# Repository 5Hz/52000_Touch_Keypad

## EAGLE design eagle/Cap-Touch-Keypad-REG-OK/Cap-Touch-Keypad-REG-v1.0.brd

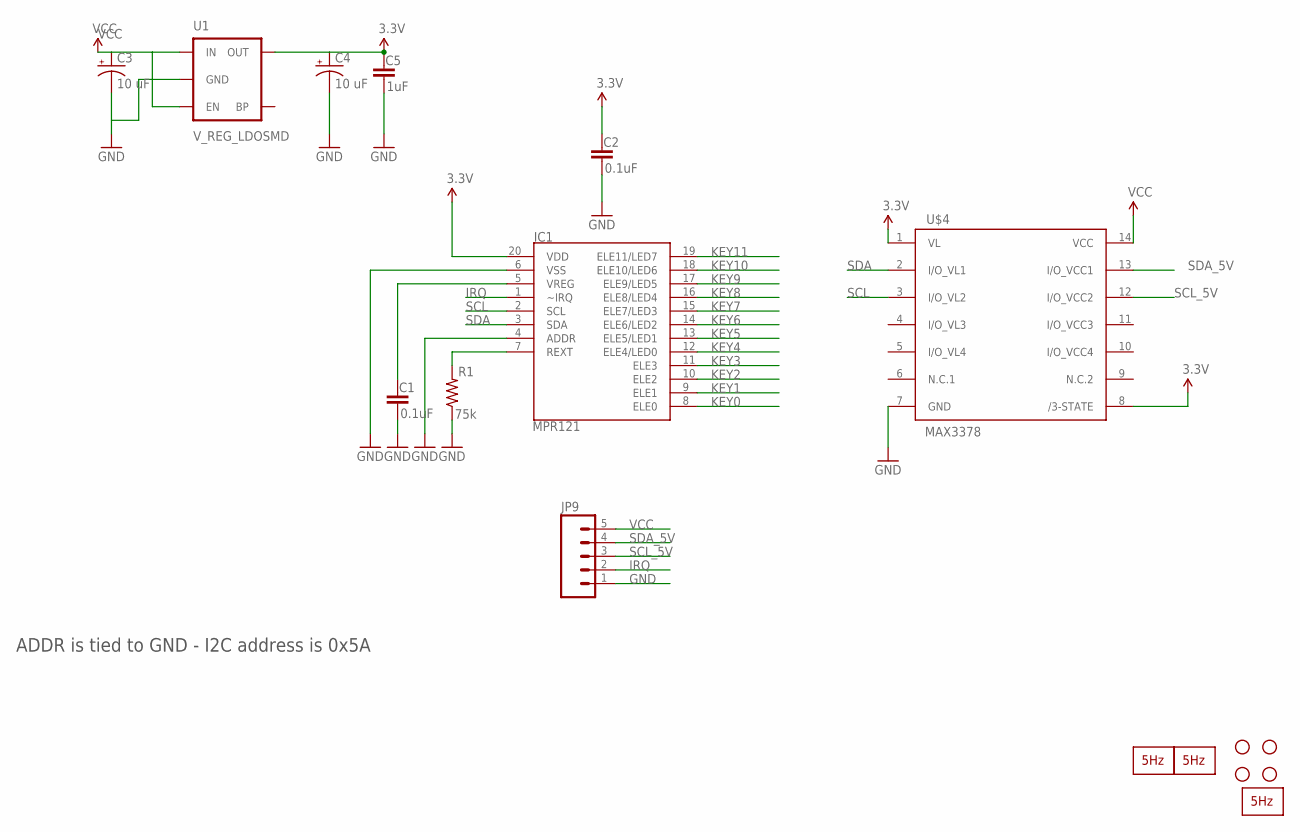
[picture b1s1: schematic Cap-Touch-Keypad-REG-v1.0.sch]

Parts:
C1, C2: 0.1uF; 0402-CAP
C3, C4: 10 uF; EIA3216
C5: 1uF; 0402-CAP
IC1: MPR121; QFN-20-0.4MM
JP3, JP4, JP7, JP8: STAND-OFF
JP9: M05PTH; 1X05
R1: 75k; 0402-RES
U1: V_REG_LDOSMD; SOT23-5
U$1: LOGO2_SILKL20MM; LARGO2_20MM
U$2, U$3: LOGO2_SILKC5MM; CIRCULO2_5MM
U$4: MAX3378; TSSOP14

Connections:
3.3V: C2.1, C4.A (+), C5.1, IC1.20 (VDD), U1.5 (OUT), U$4.1 (VL), U$4.8 (/3-STATE)
GND: C1.2, C2.2, C3.C (-), C4.C (-), C5.2, IC1.4 (ADDR), IC1.6 (VSS), JP9.1, R1.1, U1.2 (GND), U$4.7 (GND)
IRQ: IC1.1 (~IRQ), JP9.2
KEY0: IC1.8 (ELE0)
KEY1: IC1.9 (ELE1)
KEY2: IC1.10 (ELE2)
KEY3: IC1.11 (ELE3)
KEY4: IC1.12 (ELE4/LED0)
KEY5: IC1.13 (ELE5/LED1)
KEY6: IC1.14 (ELE6/LED2)
KEY7: IC1.15 (ELE7/LED3)
KEY8: IC1.16 (ELE8/LED4)
KEY9: IC1.17 (ELE9/LED5)
KEY10: IC1.18 (ELE10/LED6)
KEY11: IC1.19 (ELE11/LED7)
REXT: IC1.7 (REXT), R1.2
SCL: IC1.2 (SCL), U$4.3 (I/O_VL2)
SCL_5V: JP9.3, U$4.12 (I/O_VCC2)
SDA: IC1.3 (SDA), U$4.2 (I/O_VL1)
SDA_5V: JP9.4, U$4.13 (I/O_VCC1)
VCC: C3.A (+), JP9.5, U1.1 (IN), U1.3 (EN), U$4.14 (VCC)
VREG: C1.1, IC1.5 (VREG)

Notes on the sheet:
ADDR is tied to GND - I2C address is 0x5A

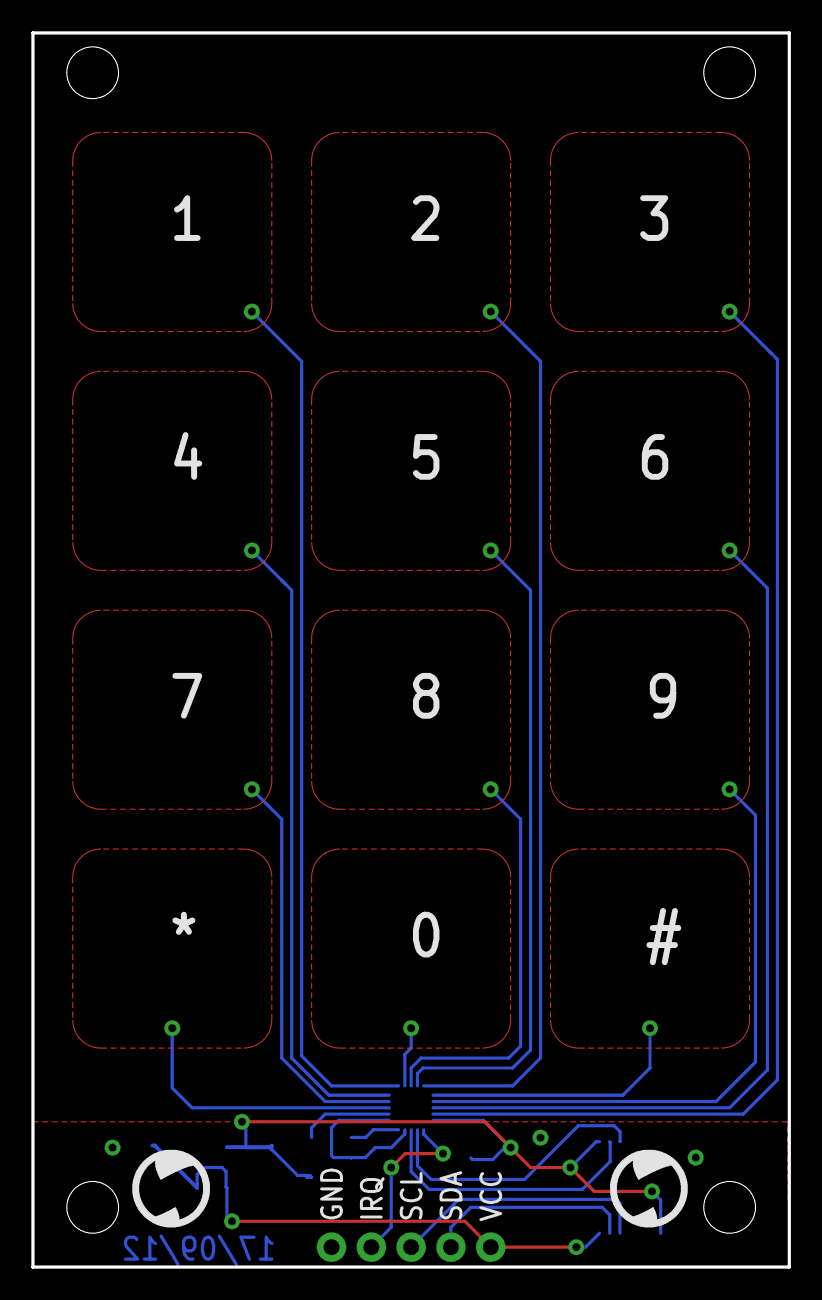
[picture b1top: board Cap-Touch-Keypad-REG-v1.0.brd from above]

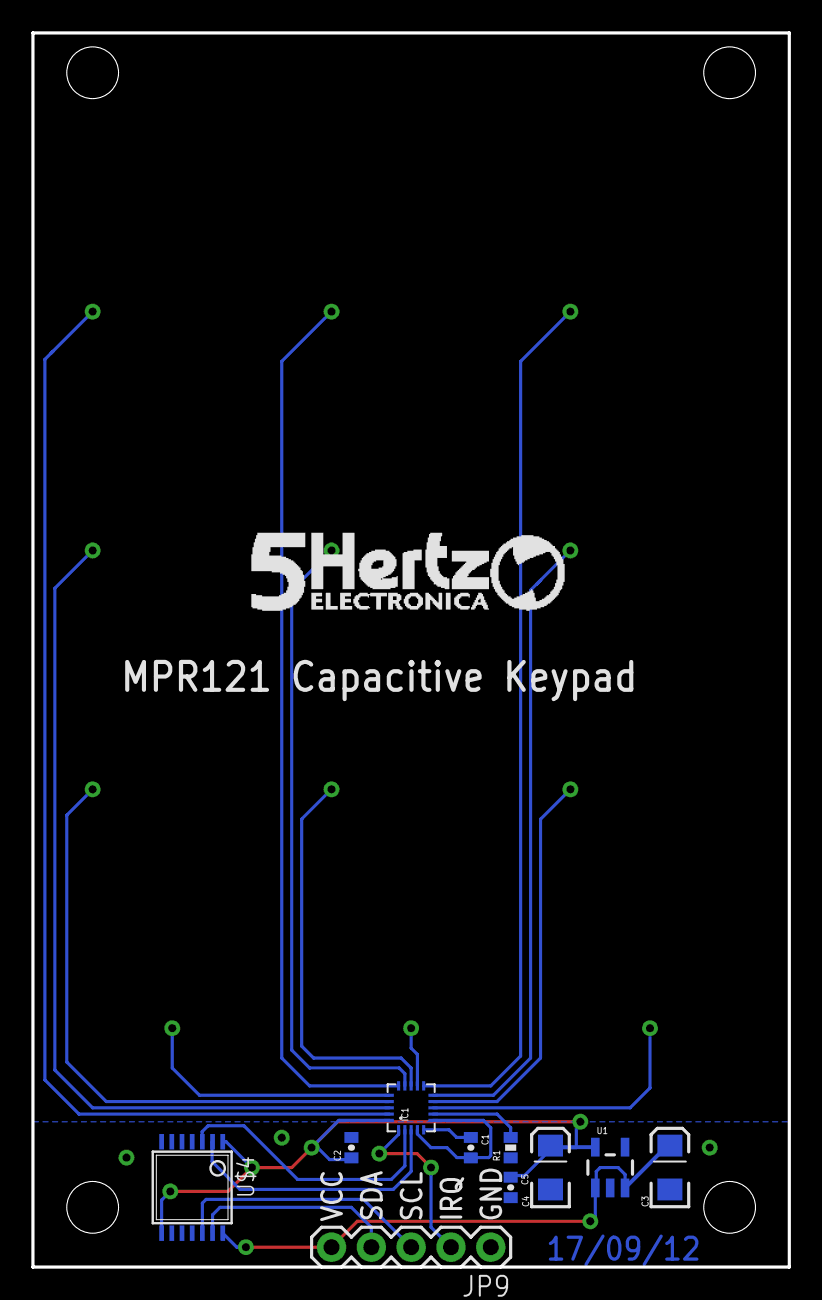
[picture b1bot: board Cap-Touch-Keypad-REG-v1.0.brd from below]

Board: 2 copper layers, 48.3 x 78.7 mm, 17 parts (15 on the bottom side), 10 nets.

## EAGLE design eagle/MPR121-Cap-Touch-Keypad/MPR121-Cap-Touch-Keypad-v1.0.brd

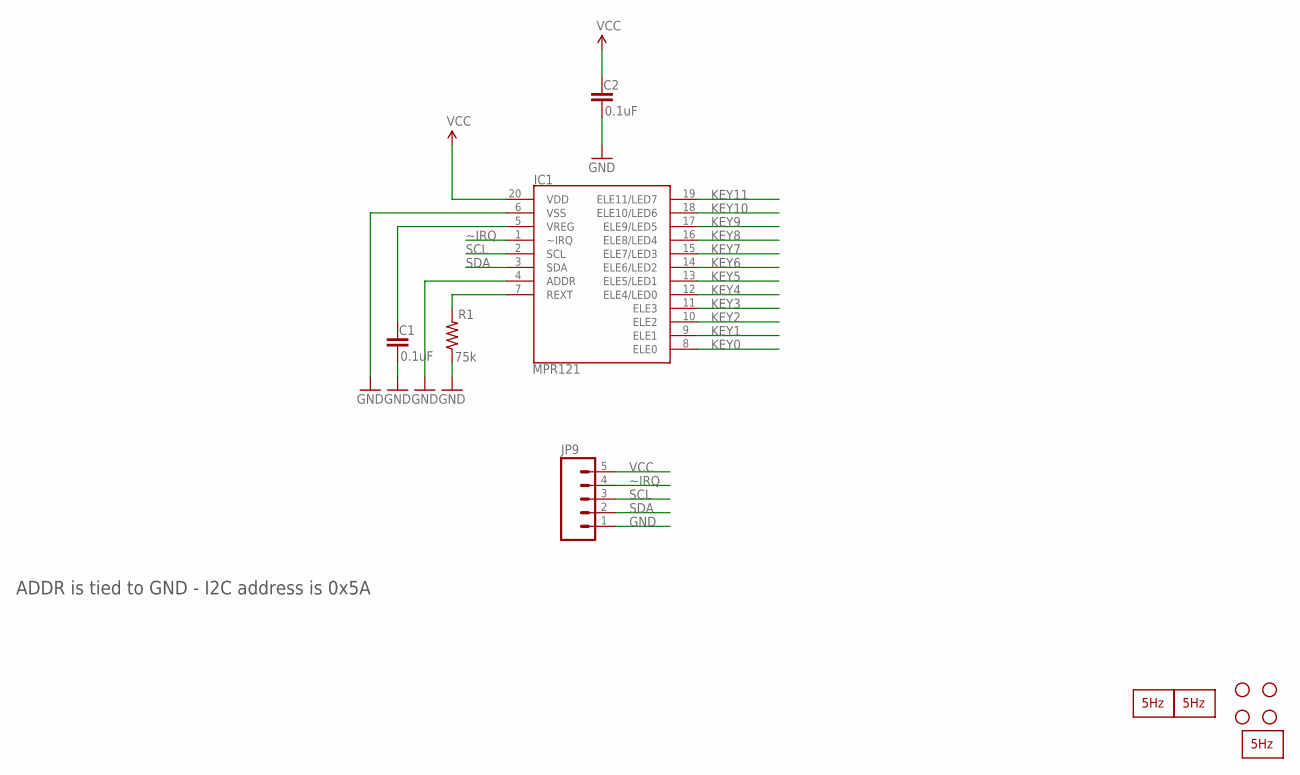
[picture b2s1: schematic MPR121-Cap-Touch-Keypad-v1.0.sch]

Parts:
C1, C2: 0.1uF; 0402-CAP
IC1: MPR121; QFN-20-0.4MM
JP3, JP4, JP7, JP8: STAND-OFF
JP9: M05PTH; 1X05
R1: 75k; 0402-RES
U$1: LOGO2_SILKL20MM; LARGO2_20MM
U$2, U$3: LOGO2_SILKC5MM; CIRCULO2_5MM

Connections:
GND: C1.2, C2.2, IC1.4 (ADDR), IC1.6 (VSS), JP9.1, R1.1
KEY0: IC1.8 (ELE0)
KEY1: IC1.9 (ELE1)
KEY2: IC1.10 (ELE2)
KEY3: IC1.11 (ELE3)
KEY4: IC1.12 (ELE4/LED0)
KEY5: IC1.13 (ELE5/LED1)
KEY6: IC1.14 (ELE6/LED2)
KEY7: IC1.15 (ELE7/LED3)
KEY8: IC1.16 (ELE8/LED4)
KEY9: IC1.17 (ELE9/LED5)
KEY10: IC1.18 (ELE10/LED6)
KEY11: IC1.19 (ELE11/LED7)
REXT: IC1.7 (REXT), R1.2
SCL: IC1.2 (SCL), JP9.3
SDA: IC1.3 (SDA), JP9.2
VCC: C2.1, IC1.20 (VDD), JP9.5
VREG: C1.1, IC1.5 (VREG)
~IRQ: IC1.1 (~IRQ), JP9.4

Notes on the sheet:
ADDR is tied to GND - I2C address is 0x5A

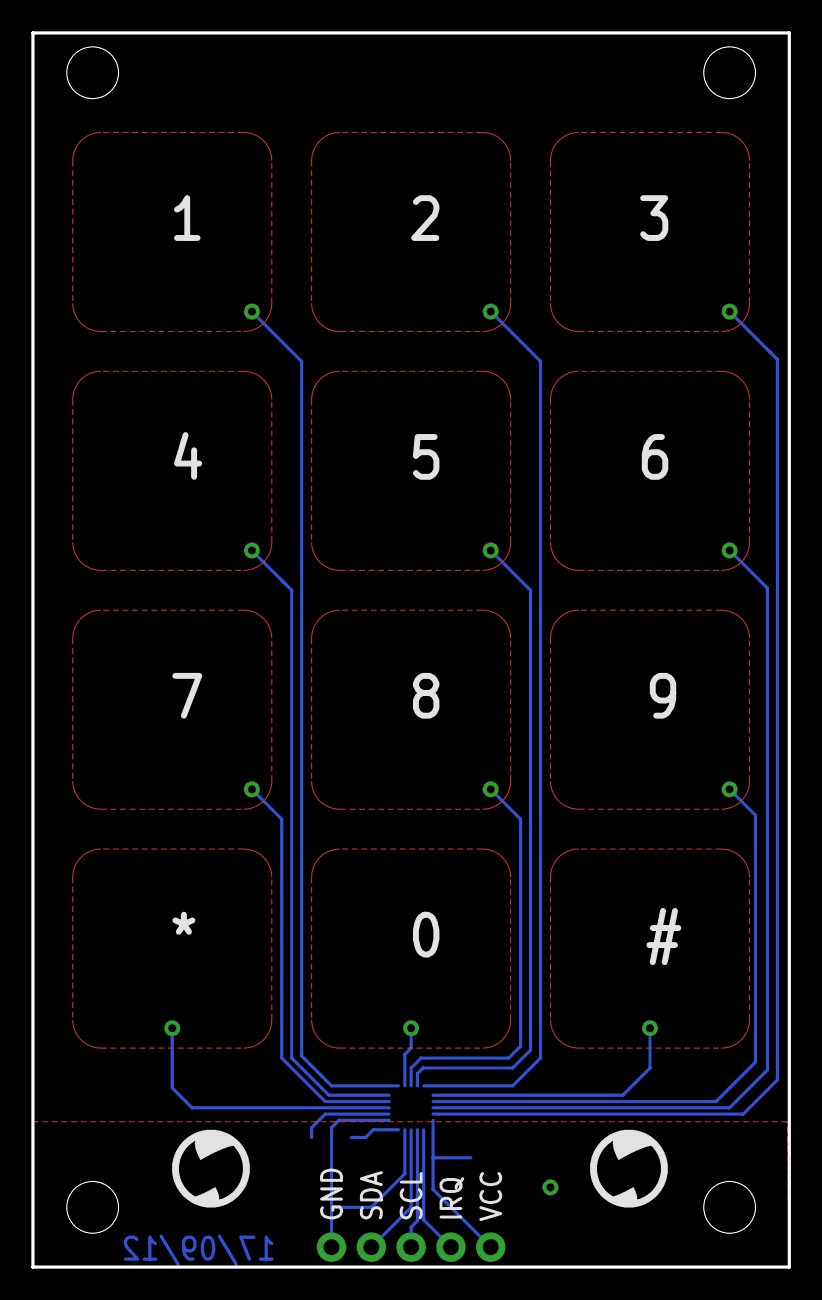
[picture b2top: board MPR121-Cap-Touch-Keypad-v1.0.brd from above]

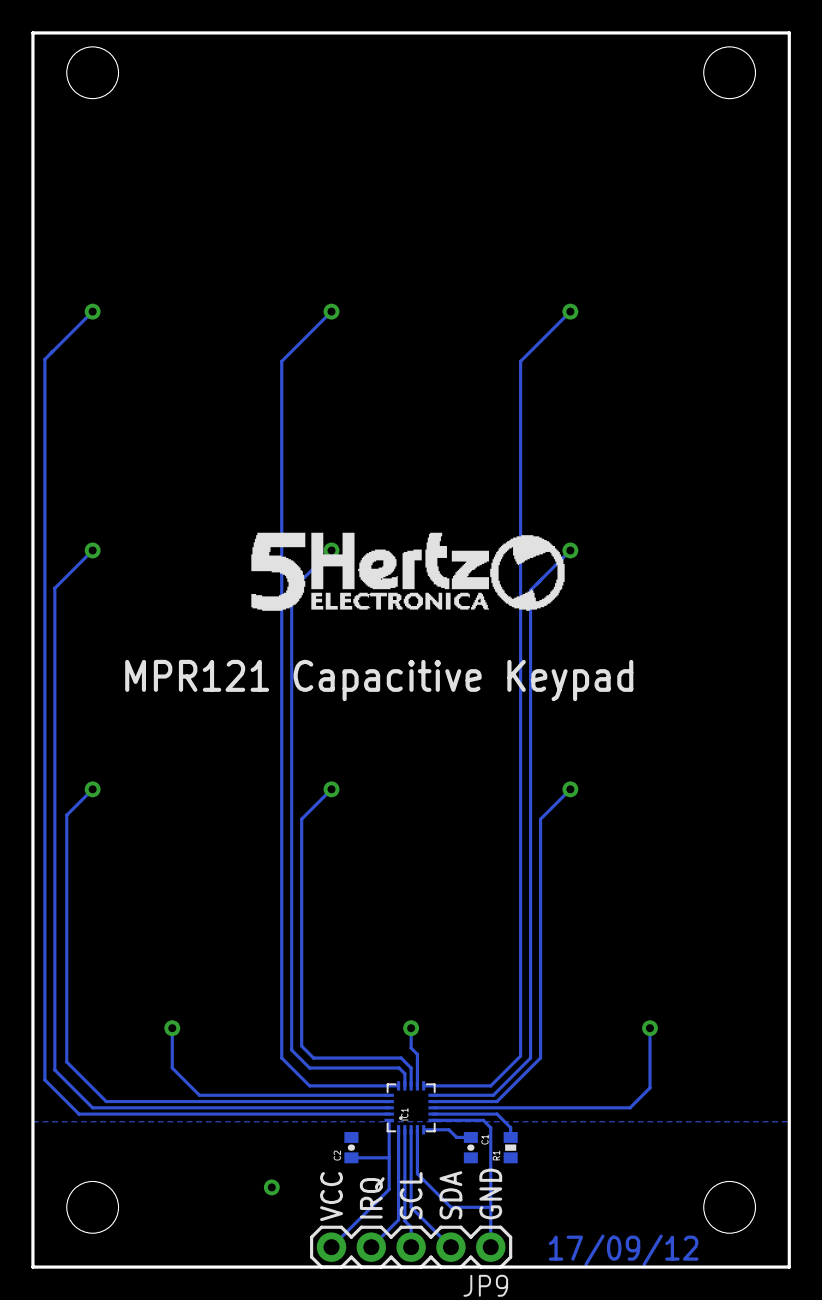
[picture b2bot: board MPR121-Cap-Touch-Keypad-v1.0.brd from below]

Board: 2 copper layers, 48.3 x 78.7 mm, 12 parts (10 on the bottom side), 7 nets.

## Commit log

2014-01-09 creacion
2014-01-09 Borrado de archivos temporales
